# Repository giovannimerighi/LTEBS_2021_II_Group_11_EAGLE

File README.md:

# LTEBS_2021_II_Group_11_EAGLE

**Final Version**

The purpose of this project consists in designing a PCB embedding the PSoC 5LP micro-controller in order to evaluate the performance of the micro-controller itself 
to assess if such uC is suitable for the project requested by the customer.
The deisgned PCB embeds the CY8CKIT-059, namely the development kit for the PSoC 5LP, and additional components required to perform the testing.

The project involves, in addition to the schematic and the board desing, a library containing custom components and Design Rules implemented according to the technical 
specifications reported in the website of the manufacturer, namely the MDSrl.

---

## Contributors
* Alessia Pesenti
* Elena Stocco
* Giovanni Merighi

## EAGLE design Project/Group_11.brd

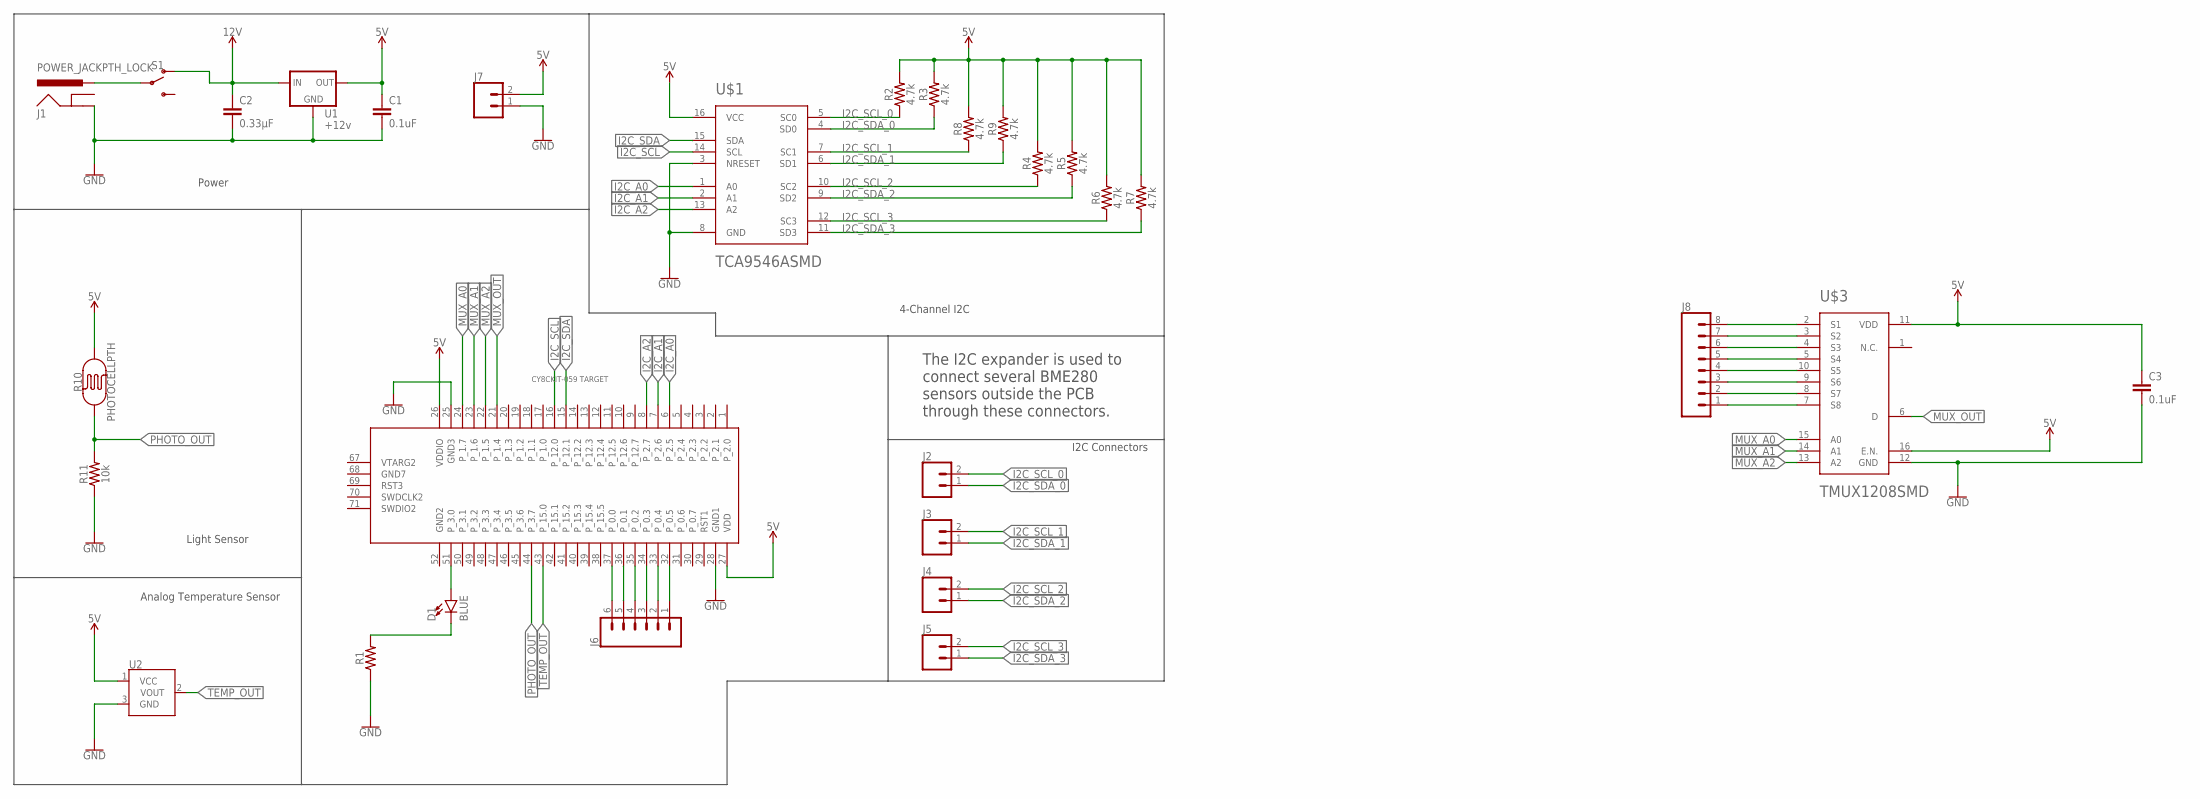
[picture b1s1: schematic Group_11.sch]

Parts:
C1, C3: 0.1uF; CAP-PTH-SMALL-KIT
C2: 0.33µF; 0805
D1: BLUE; LED-1206
J1: POWER_JACKPTH_LOCK; POWER_JACK_PTH_LOCK
J2, J3, J4, J5, J7: CONN_02; 1X02
J6: CONN_06LOCK; 1X06_LOCK
J8: CONN_08LOCK; 1X08_LOCK
R1: AXIAL-0.3
R2, R3, R4, R5, R6, R7, R8, R9: 4.7k; 0603
R10: PHOTOCELLPTH; PHOTOCELL
R11: 10k; 0603
S1: SWITCH-SPDT-PTH-11.6X4.0MM; SWITCH_SPDT_PTH_11.6X4.0MM
U1: +12v; TO-252
U2: TMP36GT9; TO-92
U$1: TCA9546ASMD; TSSOP-16
U$2: CY8CKIT-059_TARGET
U$3: TMUX1208SMD; QFN16

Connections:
5V: C1.1, C3.1, J7.2, R2.2, R3.2, R4.2, R5.2, R6.2, R7.2, R8.2, R9.2, R10.2, U1.2 (OUT), U2.1 (VCC), U$1.16 (VCC), U$2.26 (VDDIO), U$2.27 (VDD), U$3.11 (VDD), U$3.16 (E.N.)
12V: C2.1, S1.1 (O), U1.1 (IN)
GND: C1.2, C2.2, C3.2, J1.GND, J7.1, R1.P$1 (1), R11.1, U1.3 (GND), U2.3 (GND), U$1.3 (NRESET), U$1.8 (GND), U$2.25 (GND3), U$2.28 (GND1), U$3.12 (GND)
I2C_A0: U$1.1 (A0), U$2.6 (P_2.5)
I2C_A1: U$1.2 (A1), U$2.7 (P_2.6)
I2C_A2: U$1.13 (A2), U$2.8 (P_2.7)
I2C_SCL: U$1.14 (SCL), U$2.16 (P_12.0)
I2C_SCL_0: J2.2, R2.1, U$1.5 (SC0)
I2C_SCL_1: J3.2, R8.1, U$1.7 (SC1)
I2C_SCL_2: J4.2, R4.1, U$1.10 (SC2)
I2C_SCL_3: J5.2, R6.1, U$1.12 (SC3)
I2C_SDA: U$1.15 (SDA), U$2.15 (P_12.1)
I2C_SDA_0: J2.1, R3.1, U$1.4 (SD0)
I2C_SDA_1: J3.1, R9.1, U$1.6 (SD1)
I2C_SDA_2: J4.1, R5.1, U$1.9 (SD2)
I2C_SDA_3: J5.1, R7.1, U$1.11 (SD3)
MUX_A0: U$2.24 (P_1.7), U$3.15 (A0)
MUX_A1: U$2.23 (P_1.6), U$3.14 (A1)
MUX_A2: U$2.22 (P_1.5), U$3.13 (A2)
MUX_OUT: U$2.21 (P_1.4), U$3.6 (D)
unnamed: J8.8, U$3.2 (S1)
unnamed: D1.C, R1.P$2 (2)
unnamed: D1.A, U$2.51 (P_3.0)
unnamed: J6.6, U$2.37 (P_0.0)
unnamed: J6.5, U$2.36 (P_0.1)
unnamed: J6.4, U$2.35 (P_0.2)
unnamed: J6.3, U$2.34 (P_0.3)
unnamed: J6.2, U$2.33 (P_0.4)
unnamed: J1.PWR, S1.2
unnamed: J8.7, U$3.3 (S2)
unnamed: J8.1, U$3.7 (S8)
unnamed: J8.2, U$3.8 (S7)
unnamed: J8.3, U$3.9 (S6)
unnamed: J8.4, U$3.10 (S5)
unnamed: J8.5, U$3.5 (S4)
unnamed: J8.6, U$3.4 (S3)
unnamed: J6.1, U$2.32 (P_0.5)
PHOTO_OUT: R10.1, R11.2, U$2.44 (P_3.7)
TEMP_OUT: U2.2 (VOUT), U$2.43 (P_15.0)

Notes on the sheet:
Light Sensor
Analog Temperature Sensor
Power
I2C Connectors
The I2C expander is used to connect several BME280 sensors outside the PCB through these connectors.
4-Channel I2C

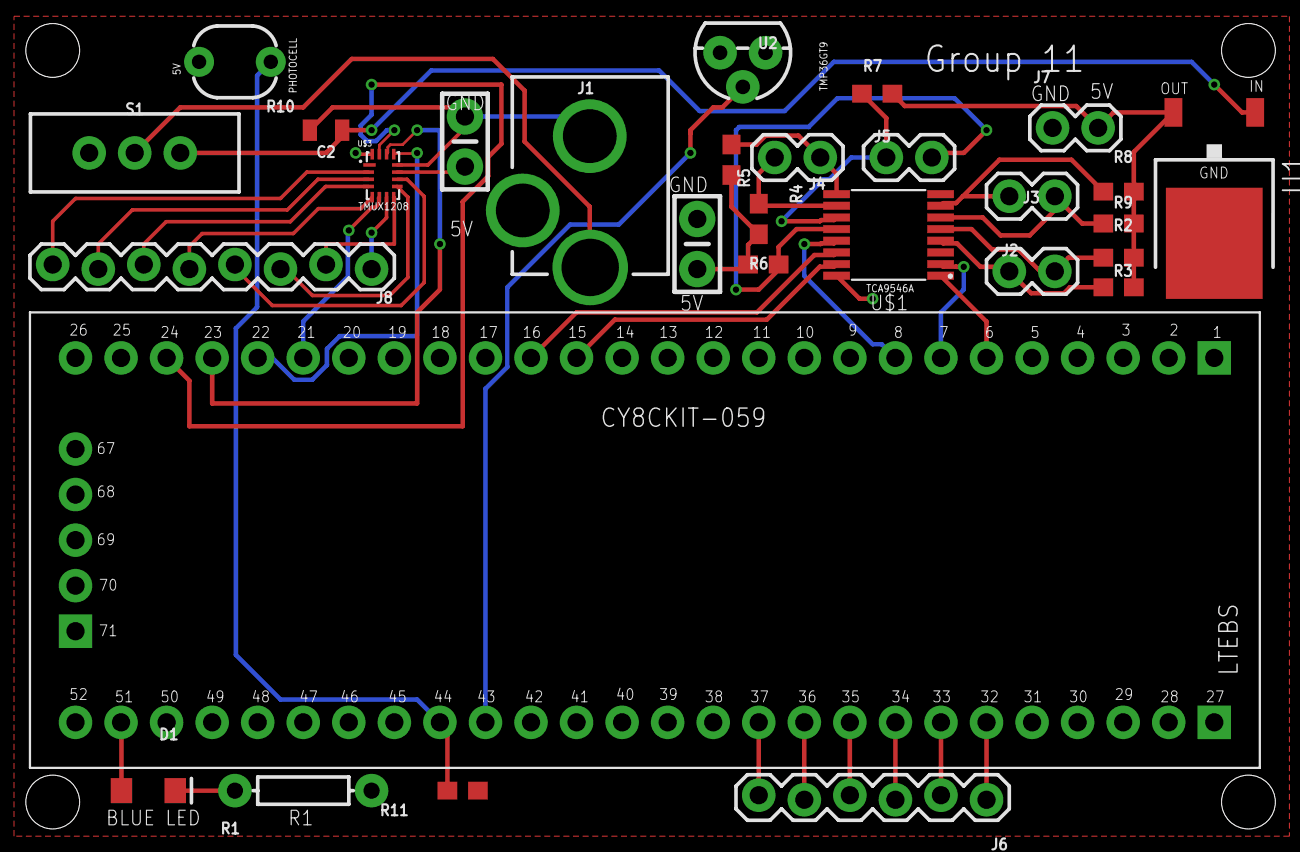
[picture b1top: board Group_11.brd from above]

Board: 2 copper layers, 29 parts (0 on the bottom side), 39 nets.

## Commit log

2021-03-18 Creazione TCA9546A in libreria
2021-03-18 Modifica NRESET
2021-03-18 Prima Versione Schematico
2021-03-19 Aggiunta dei Labels alla prima versione dello schematico
2021-03-20 Organizzazione in cartelle
2021-03-20 Modifica Labels I2C_SCL
2021-03-20 Aggiunta TMUX1208 alla libreria
2021-03-20 Modifica di libreria e schematico su dev
2021-03-20 Prima commit Board
2021-03-20 Modifica symbols e schematico aggiornato
2021-03-20 Modifica Libreria
2021-03-20 Aggiornamento board
2021-03-21 Aggiunta GND
2021-03-21 Aggiornamento parte inferiore
2021-03-21 Aggiunta file Design Rules, prima versione
2021-03-21 Board da verificare con Design Rules
2021-03-21 Prova disposizione board
2021-03-21 Aggiunta dei quattro fori alla board e riorganizzazione dei componenti
2021-03-22 Versione corretta con path da 8 mil nel mux, holes da 3mm
2021-03-22 Board senza errori
2021-03-22 Correzione schematico collegamenti MUX
2021-03-22 Aggiunta collegamenti board
2021-03-22 Correzione clearance
2021-03-22 Salvataggio per merge
2021-03-23 Modifica design rules
2021-03-23 Aggiunta silkscreen
2021-03-24 Modifica isolate settings
2021-03-25 Versione Revisionata
2021-03-25 Dimensioni board
2021-03-25 Aggiornamento gitignore
2021-03-26 Modifica silkscreen
2021-03-26 Aggiunta isolation
2021-03-26 Final version

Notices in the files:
parts and their libraries:
SparkFun-Aesthetics: Licensing: Creative Commons ShareAlike 4.0 International - https://creativecommons.org/licenses/by-sa/4.0
